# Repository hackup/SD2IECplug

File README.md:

SD2IEC Pluggable
================

* KiCAD project files for my take on a [SD2IEC](http://www.pitsch.de/stuff/mmc2iec/) compatible board.
* The schematics are heavily based on the [design by Shadowolf](https://www.forum64.de/index.php?thread/21242-sd2iec-hardware-1-0/).
* The [BOM export](SD2IECplug-BOM.csv) is included in the repository.
* There should probably be more documentation here, but while it is still missing you may find some additional information [on my blog](https://www.hackup.net/tag/sd2iec/).
* This is all work in progress with absolutely no guarantees. **USE AT YOUR OWN RISK!**

### Revision 2

In revision 2, the PCB size has been reduced by more than 50% and TAPuino support has been ditched. It now features a Micro SD slot and a few other improvements. Note: In this revision, the numbering of the LEDs has been accidentally reversed. This has been fixed later on the master branch.

### Revision 1

The first revision required a much larger PCB but featured a full-size SD slot and experimental support for TAPuino functionality. The latter was never tested though and probably wouldn't work.

If you don't intend to use the TAPuino functionality (and there isn't any firmware support for this yet) you can omit R16-R21 and the optocoupler U3. Also, the board can be power either through the USB or the tape port connector so you don't necessarily need to fit both.

## License
[
](http://creativecommons.org/licenses/by-nc-sa/4.0/)

This work is licensed under a
[Creative Commons Attribution-NonCommercial-ShareAlike 4.0 International License](http://creativecommons.org/licenses/by-nc-sa/4.0/).

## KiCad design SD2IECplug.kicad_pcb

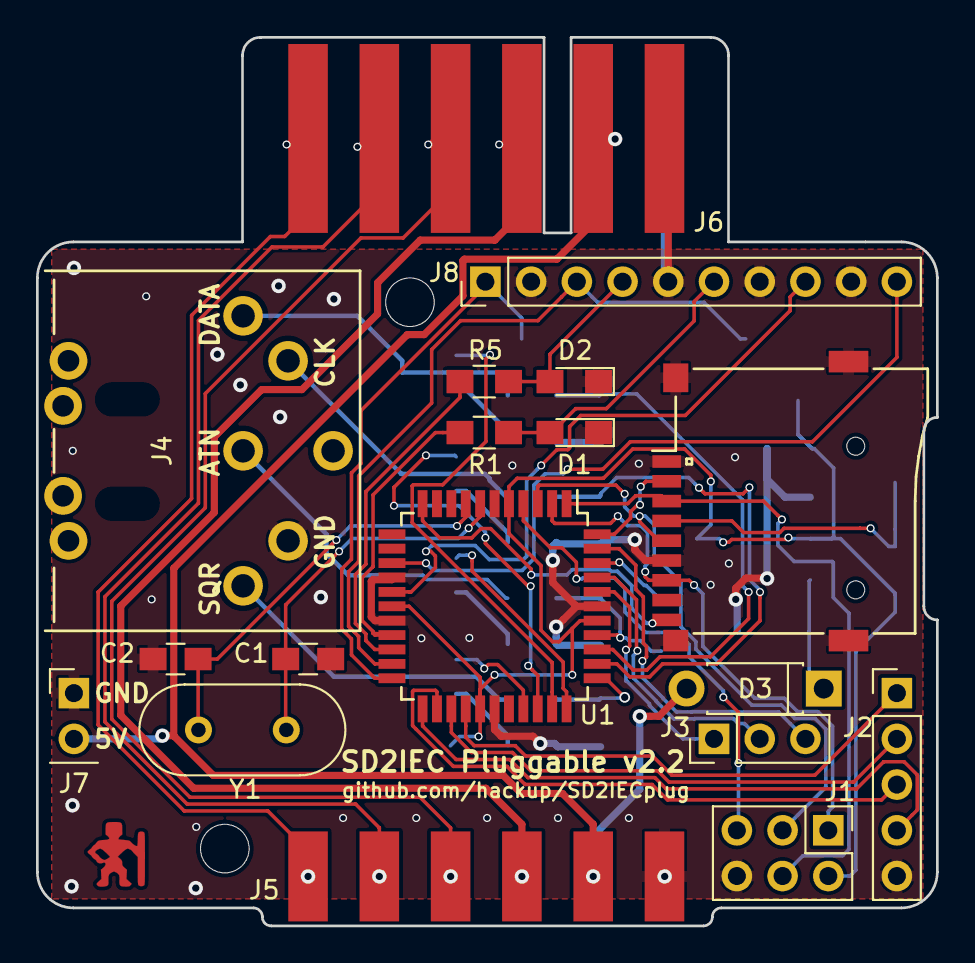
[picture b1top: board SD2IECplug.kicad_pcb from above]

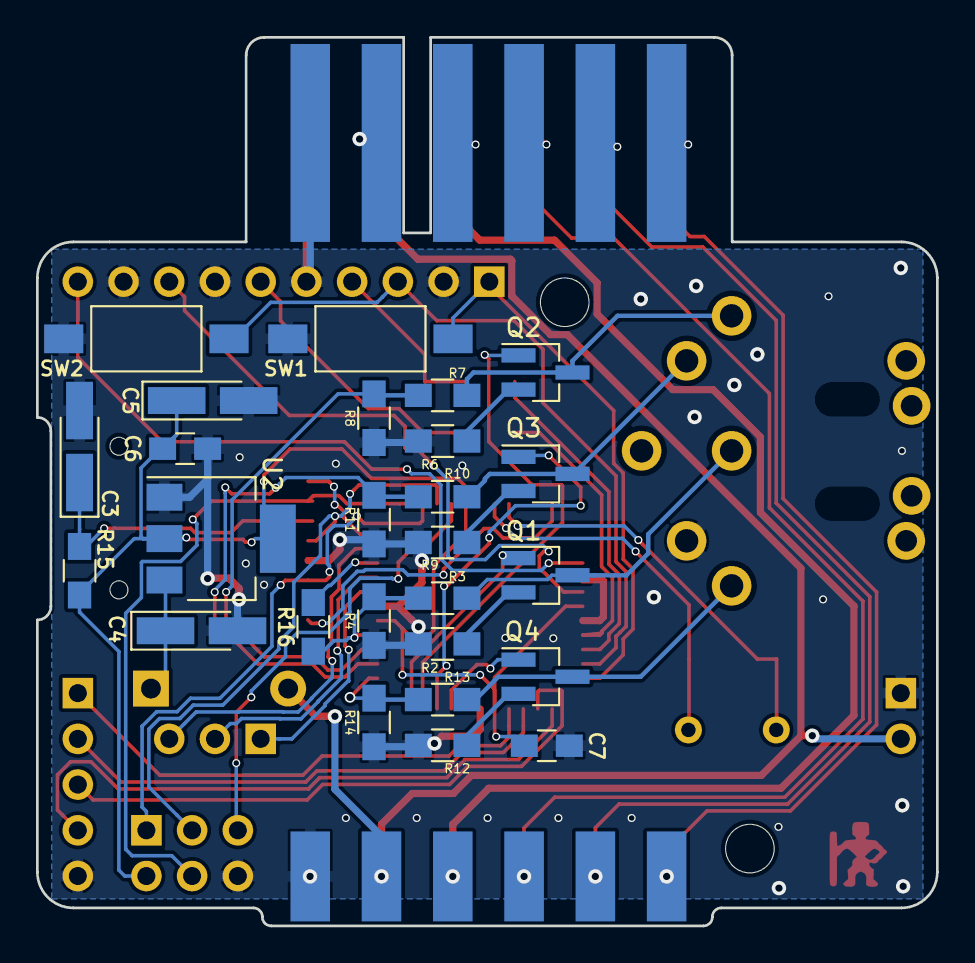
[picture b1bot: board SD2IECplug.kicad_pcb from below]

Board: 2 copper layers, 50.0 x 49.4 mm, 48 parts (26 on the bottom side), 49 nets.

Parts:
C1, C2: 56p; C_0805_HandSoldering
C3, C4, C5: 10µ; CP_Tantalum_Case-S_EIA-3216-12_Hand
C6, C7: 100n; C_0805_HandSoldering
D1: red; LED_0805_HandSoldering
D2: green; LED_0805_HandSoldering
D3: 1N5817; D_DO-41_SOD81_P7.62mm_Horizontal
J1: ISP; Pin_Header_Straight_2x03_Pitch2.54mm
J2: X6; Pin_Header_Straight_1x05_Pitch2.54mm
J3: Aux; Pin_Header_Straight_1x03_Pitch2.54mm
J4: IEC; DIN-6-Variable
J5: C64-CassettePort; C64-Cassette-Port-Female
J6: C64-CassettePort; C64-Cassette-Port-Male
J7: Power; Pin_Header_Straight_1x02_Pitch2.54mm
J8: X3; Pin_Header_Straight_1x10_Pitch2.54mm
MH1, MH2: ZipTie; ZipTie_3.0mm
MH3, MH4: MountingHole; MountingHole_2.7mm_M2.5
Q1, Q2, Q3, Q4: BSS138; SOT-23_Handsoldering
R1, R5: 330; R_0805_HandSoldering
R2, R6, R9, R12: 18; R_0805_HandSoldering
R3, R7, R10, R13: 10k; R_0805_HandSoldering
R4, R8, R11, R14: 22k; R_0805_HandSoldering
R15: 2.2R; R_0805_HandSoldering
R16: nB; R_0805_HandSoldering
SW1, SW2: SW_Push; SW_SPST_FSMSM
U1: ATMEGA644-20AU; TQFP-44_10x10mm_Pitch0.8mm
U2: AMS1117-3.3; SOT-223-3_TabPin2
XS1: SD Connector; Conn_uSDcard
Y1: 8MHz; Crystal_HC49-4H_Vertical

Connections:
+3V3: C5.1, C6.1, C7.1, J1.2, R15.2, U1.5, U1.17, U1.27, U1.38, U2.2
/DISKSWITCH: J8.1, SW1.1, U1.22
/IEC_8-9: J8.8, U1.16
/IEC_10-11: J8.10, U1.14
/LED1: D1.2, J8.4, R5.1
/LED2: D2.2, J8.6, R1.1
/RESERVE: J8.3, SW2.1, U1.21
Cas-5V: D3.2, J5.2, J5.B, J6.2, J6.B, J7.2
Cas-GND: C1.1, C2.1, C3.2, C4.2, C5.2, C6.2, C7.2, D1.1, D2.1, J1.6, J2.5, J4.2, J5.1, J5.A, J6.1, J6.A, J7.1, J8.2, J8.5, J8.7, J8.9, R2.2, R4.2, R6.2, R8.2, R9.2, R11.2, R12.2, R14.2, SW1.2, SW2.2, U1.6, U1.15, U1.18, U1.28, U1.39, U2.1, XS1.1, XS1.6, XS1.8
Cas-Motor: J5.3, J5.C, J6.3, J6.C
Cas-Read: J5.4, J5.D, J6.4, J6.D
Cas-Sense: J5.6, J5.F, J6.6, J6.F
Cas-Write: J5.5, J5.E, J6.5, J6.E
IEC_ATN: J4.3, Q1.3, R3.1
IEC_CLK: J4.4, Q3.3, R10.1
IEC_DATA: J4.5, Q2.3, R7.1
IEC_SQR: J4.1, Q4.3, R13.1
MISO: J1.1, U1.2, XS1.7
MOSI: J1.4, U1.1, XS1.3
unnamed: C1.2, U1.7, Y1.2
unnamed: C2.2, U1.8, Y1.1
unnamed: C3.1, R15.1, XS1.4
unnamed: C4.1, D3.1, U2.3
unnamed: J1.5, U1.4
unnamed: J2.1, U1.26
unnamed: J2.2, U1.25
unnamed: J2.3, U1.24
unnamed: J2.4, U1.23
unnamed: J3.1, U1.40
unnamed: J3.2, U1.41
unnamed: J3.3, U1.43
unnamed: Q1.1, U1.33
unnamed: Q1.2, R2.1
unnamed: Q2.1, U1.32
unnamed: Q2.2, R6.1
unnamed: Q3.1, U1.31
unnamed: Q3.2, R9.1
unnamed: Q4.1, U1.30
unnamed: Q4.2, R12.1
unnamed: R1.2, U1.19
unnamed: R5.2, U1.20
unnamed: R7.2, R8.1, U1.36
unnamed: R10.2, R11.1, U1.35
unnamed: R13.2, R14.1, U1.34
unnamed: R3.2, R4.1, R16.1, U1.37
unnamed: R16.2, U1.42
unnamed: U1.11, XS1.9
unnamed: U1.44, XS1.2
SCK: J1.3, U1.3, XS1.5

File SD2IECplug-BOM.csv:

Title,SD2IEC Pluggable
Revision,2.1
Date,2019-12-18
Generated,18/12/2019 10:01:49
Company,www.hackup.net
Comment 1,
Comment 2,
Comment 3,
Comment 4,
Total Parts,48
Total Unique Parts,29



Ref,Qty,Value,Footprint,Datasheet,Manf,Manf#,
C1 C2 ,2,56p,Capacitors_SMD:C_0805_HandSoldering,, , 
C3 C4 C5 ,3,10µ,Capacitors_Tantalum_SMD:CP_Tantalum_Case-S_EIA-3216-12_Hand,, , 
C6 ,1,100n,Capacitors_SMD:C_0805_HandSoldering,, , 
C7 ,1,100n,Capacitors_SMD:C_0805_HandSoldering,~, , 
D1 ,1,red,LEDs:LED_0805_HandSoldering,, , 
D2 ,1,green,LEDs:LED_0805_HandSoldering,, , 
D3 ,1,1N5817,Diodes_THT:D_DO-41_SOD81_P7.62mm_Horizontal,, , 
J1 ,1,ISP,Pin_Headers:Pin_Header_Straight_2x03_Pitch2.54mm,, , 
J2 ,1,X6,Pin_Headers:Pin_Header_Straight_1x05_Pitch2.54mm,~, , 
J3 ,1,Aux,Pin_Headers:Pin_Header_Straight_1x03_Pitch2.54mm,~, , 
J4 ,1,IEC,DIN-Connectors:DIN-6-Variable,, , 
J5 ,1,C64-CassettePort,hackup:C64-Cassette-Port-Female,, , 
J6 ,1,C64-CassettePort,hackup:C64-Cassette-Port-Male,, , 
J7 ,1,Power,Pin_Headers:Pin_Header_Straight_1x02_Pitch2.54mm,~, , 
J8 ,1,X3,Pin_Headers:Pin_Header_Straight_1x10_Pitch2.54mm,~, , 
MH1 MH2 ,2,ZipTie,DIN-Connectors:ZipTie_3.0mm,~, , 
MH3 MH4 ,2,MountingHole,Mounting_Holes:MountingHole_2.7mm_M2.5,~, , 
Q1 Q2 Q3 Q4 ,4,BSS138,TO_SOT_Packages_SMD:SOT-23_Handsoldering,, , 
R1 R5 ,2,330,Resistors_SMD:R_0805_HandSoldering,, , 
R2 R6 R9 R12 ,4,18,Resistors_SMD:R_0805_HandSoldering,, , 
R3 R7 R10 R13 ,4,10k,Resistors_SMD:R_0805_HandSoldering,, , 
R4 R8 R11 R14 ,4,22k,Resistors_SMD:R_0805_HandSoldering,, , 
R15 ,1,2.2R,Resistors_SMD:R_0805_HandSoldering,, , 
R16 ,1,nB,Resistors_SMD:R_0805_HandSoldering,~, , 
SW1 SW2 ,2,SW_Push,Buttons_Switches_SMD:SW_SPST_FSMSM,, , 
U1 ,1,ATMEGA644-20AU,Housings_QFP:TQFP-44_10x10mm_Pitch0.8mm,, , 
U2 ,1,AMS1117-3.3,TO_SOT_Packages_SMD:SOT-223-3_TabPin2,, , 
XS1 ,1,SD Connector,lib:Conn_uSDcard,_,ebay,_
Y1 ,1,8MHz,Crystals:Crystal_HC49-4H_Vertical,, , 




BOM made with KICAD_BOM_WIZARD (https://github.com/HashDefineElectronics/KiCad_BOM_Wizard.git)
Generated 18/12/2019 10:01:49

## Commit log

2017-11-24 Inital commit.
2017-11-24 Fill areas.
2017-11-24 Keep Makefile only in gerber dir.
2017-11-24 Added optional I2C connector.
2017-11-24 Removed push button, added switch header.
2017-11-24 Added another mounting hole.
2017-11-24 Forgotten changes.
2017-12-06 Bug fix: Mini USB GND actually seems to be on pin 5.
2017-12-08 Added README.
2017-12-10 Changed diode D3 footprint.
2017-12-25 Upgraded project files.
2018-01-17 Added BOM export and notes.
2018-09-10 First steps.
2018-09-10 First routing.
2018-09-11 Indent PCB for SD card.
2018-09-11 Moced SD connector.
2018-09-11 Ziptie holes and silk screen cleanup.
2018-09-12 Improved routing.
2018-09-12 Added missing resistor and yet another breakout header.
2018-09-12 Aligned connectors to grid.
2018-09-12 Added mounting hole.
2018-09-12 Increased motor line track width.
2018-09-12 Aligned external power connector.
2018-09-12 Added decoupling cap.
2018-09-12 Added push buttons.
2018-09-12 Old gerber files.
2018-09-12 Fixed board edge.
2018-09-13 Reduced silk screen outline.
2018-09-13 Round SD card recess.
2018-09-14 Ordered prototype batch of 4x4 panels.
2018-10-08 Corrected ground plane.
2018-10-08 Moved data lines further away from drill holes.
2018-10-08 Revision increment.
2018-10-08 Improved ziptie holes.
2018-10-08 IRLML2803 -> BSS138
2018-10-14 Corrected LED numbering.
2018-10-15 Updated BOM.
2018-10-31 Moved connector pads to the edge.
2018-10-31 Extrude connector pads.
2018-11-12 Added schematics export.
2019-08-16 Clarified license.
2019-12-18 Fixed symbol library references.
2019-12-18 Updated readme.
2021-01-09 Fixed library path.
2021-01-09 Placement of C3 got messed up between v0.9 and v2.0, fixes #1.
2023-01-06 Updated to KiCAD 6, fixed a few warnings.
2023-01-06 Created gerber files for latest version.
